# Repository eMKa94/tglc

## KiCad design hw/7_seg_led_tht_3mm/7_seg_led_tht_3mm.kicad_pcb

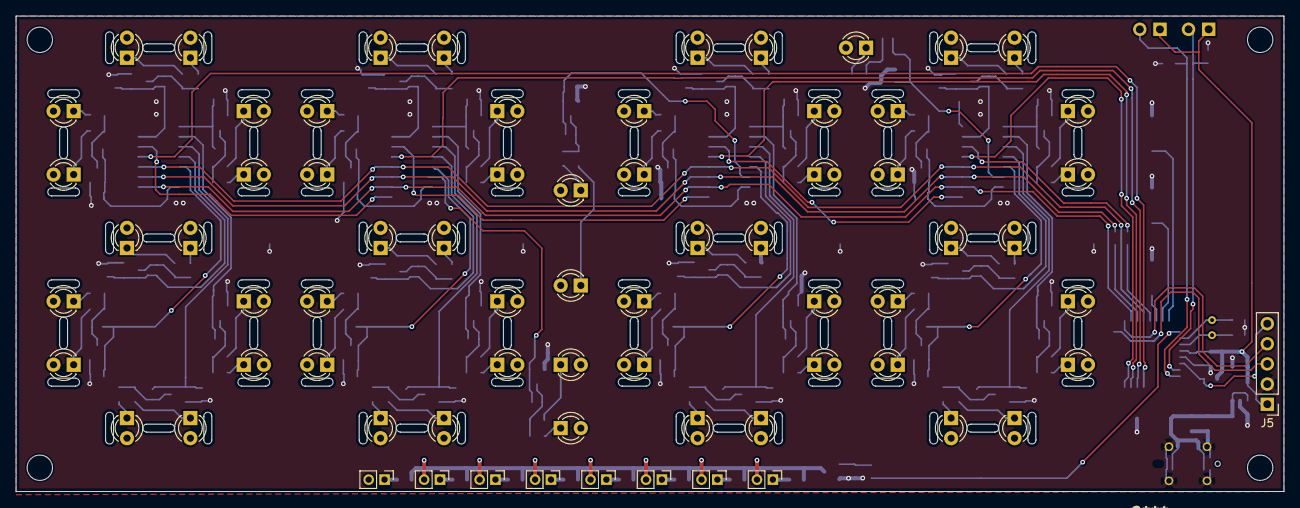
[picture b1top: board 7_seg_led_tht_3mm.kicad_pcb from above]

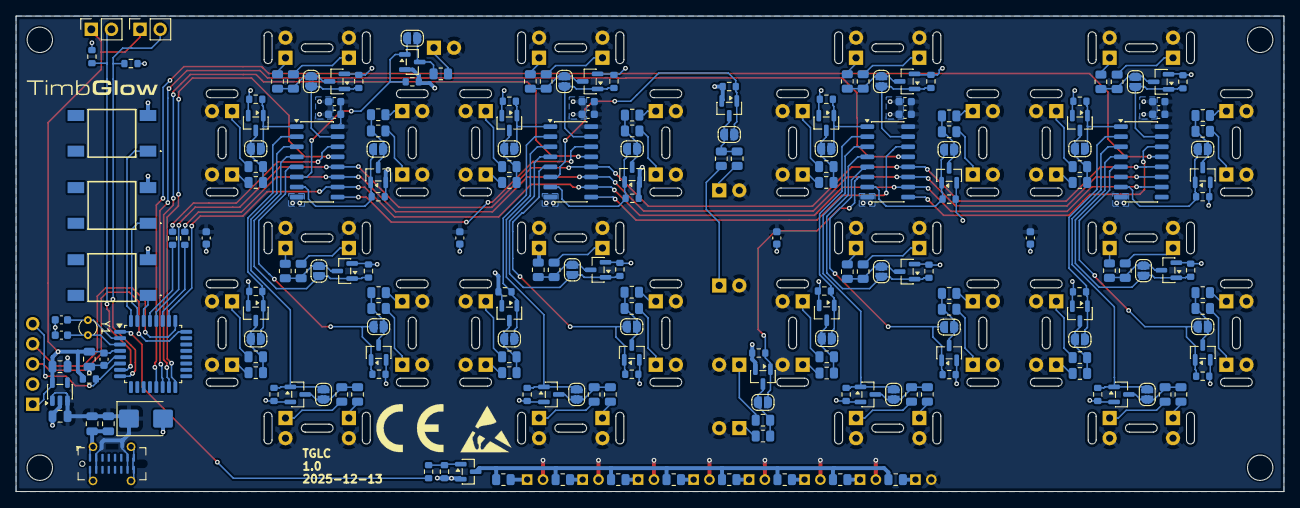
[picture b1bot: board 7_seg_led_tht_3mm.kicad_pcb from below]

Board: 2 copper layers, 160.0 x 60.0 mm, 278 parts (208 on the bottom side), 160 nets.

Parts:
C1, C2: 10u; C_0805_2012Metric
C3, C4, C8: 1u; C_0805_2012Metric
C6, C7: 7p 50V; C_0603_1608Metric
C9, C11, C13, C15, C17: 100n; C_0603_1608Metric
C10, C12, C14, C16, C18, C19, C20, C21: 1u; C_0603_1608Metric
D1: D_Zener; D_SMB
D2, D67, D68, D69, D70, D71, D72, D73: LED; PinHeader_1x02_P2.00mm_Vertical
D3, D4, D5, D6, D7, D8, D9, D10, D11, D12, D13, D14, D15, D16, D17, D19, D20, D21, D22, D23, D24, D25, D26, D27, D28, D29, D30, D31, D32, D33, D34, D35, D36, D37, D38, D39, D40, D41, D42, D43, D44, D45, D46, D47, D48, D49, D50, D51, D52, D53, D54, D55, D56, D57, D58, D59, D60, D61, D62, D63, D64: LED; LED_D3.0mm
H1, H2, H2#2, H2#3: MountingHole; MountingHole_3.2mm_M3
J1: USB_C_Plug_USB2.0; USB_C_Receptacle_G-Switch_GT-USB-7051x
J3, J4: PGM5526; PinSocket_1x02_P2.54mm_Vertical
J5: Conn_01x05; PinHeader_1x05_P2.54mm_Vertical
JP3, JP4, JP5, JP6, JP7, JP8, JP9, JP10, JP11, JP12, JP13, JP14, JP15, JP16, JP17, JP18, JP19, JP20, JP21, JP22, JP23, JP24, JP25, JP26, JP27, JP28, JP29, JP30, JP31, JP32, JP33: Jumper_2_Small_Open; SolderJumper-2_P1.3mm_Open_RoundedPad1.0x1.5mm
Q1, Q2, Q3, Q4, Q5, Q6, Q7, Q8, Q9, Q10, Q11, Q12, Q13, Q14, Q15, Q16, Q17, Q18, Q19, Q20, Q21, Q22, Q23, Q24, Q25, Q26, Q27, Q28, Q29, Q30, Q31, Q33: 2N7002K; SOT-23
R1, R3, R4: 4K7; R_0603_1608Metric
R2, R110, R111: 22; R_0603_1608Metric
R5, R7, R9, R10, R12, R13, R15, R16, R18, R19, R21, R22, R24, R25, R27, R29, R31, R33, R34, R36, R37, R39, R40, R42, R43, R45, R46, R48, R49, R51, R52, R53, R55, R57, R58, R60, R61, R63, R64, R66, R67, R69, R70, R72, R73, R75, R76, R77, R79, R81, R82, R84, R85, R87, R88, R90, R91, R93, R94, R96, R97, R101, R102, R103, R104, R105, R106, R107, R108: R; R_0805_2012Metric
R6, R8, R11, R14, R17, R20, R23, R26, R30, R32, R35, R38, R41, R44, R47, R50, R54, R56, R59, R62, R65, R68, R71, R74, R78, R80, R83, R86, R89, R92, R95, R109: 10K; R_0603_1608Metric
SW1, SW2, SW3: SW_MEC_5E; TS046673BK100SMT
U1: MIC5504-3.3YM5; SOT-23-5
U2: STM32G030K8Tx; LQFP-32_7x7mm_P0.8mm
U3, U4, U5, U6: 74HCT595; SO-16_3.9x9.9mm_P1.27mm
Y1: 32K768; Crystal_C26-LF_D2.1mm_L6.5mm_Vertical

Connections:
+5V: C1.1, C2.1, C3.1, C10.2, C11.2, C12.2, C13.2, C14.2, C15.2, C16.2, C17.2, C18.1, C19.1, C20.1, C21.1, D1.1 (K), D2.2 (A), D3.2 (A), D4.2 (A), D5.2 (A), D6.2 (A), D7.2 (A), D8.2 (A), D9.2 (A), D10.2 (A), D11.2 (A), D12.2 (A), D13.2 (A), D14.2 (A), D15.2 (A), D16.2 (A), D17.2 (A), D19.2 (A), D20.2 (A), D21.2 (A), D22.2 (A), D23.2 (A), D24.2 (A), D25.2 (A), D26.2 (A), D27.2 (A), D28.2 (A), D29.2 (A), D30.2 (A), D31.2 (A), D32.2 (A), D33.2 (A), D34.2 (A), D35.2 (A), D36.2 (A), D37.2 (A), D38.2 (A), D39.2 (A), D40.2 (A), D41.2 (A), D42.2 (A), D43.2 (A), D44.2 (A), D45.2 (A), D46.2 (A), D47.2 (A), D48.2 (A), D49.2 (A), D50.2 (A), D51.2 (A), D52.2 (A), D53.2 (A), D54.2 (A), D55.2 (A), D56.2 (A), D57.2 (A), D58.2 (A), D59.2 (A), D60.2 (A), D61.2 (A), D62.2 (A), D63.2 (A), D64.2 (A), D67.2 (A), D68.2 (A), D69.2 (A), D70.2 (A), D71.2 (A), D72.2 (A), D73.2 (A), J1.A4 (VBUS), J1.A9 (VBUS), J1.B4 (VBUS), J1.B9 (VBUS), U1.1 (VIN), U1.3 (EN), U3.16 (VCC), U4.16 (VCC), U5.16 (VCC), U6.16 (VCC)
/7_SEG_1/A: JP3.2 (B), Q1.3 (D), R5.1, R7.1
/7_SEG_1/B: JP4.2 (B), Q2.3 (D), R9.1, R10.1
/7_SEG_1/C: JP5.2 (B), Q3.3 (D), R12.1, R13.1
/7_SEG_1/D: JP6.2 (B), Q4.3 (D), R15.1, R16.1
/7_SEG_1/E: JP7.2 (B), Q5.3 (D), R18.1, R19.1
/7_SEG_1/F: JP8.2 (B), Q6.3 (D), R21.1, R22.1
/7_SEG_1/G: JP9.2 (B), Q7.3 (D), R24.1, R25.1
/7_SEG_1/H: JP10.2 (B), Q8.3 (D), R27.1
/7_SEG_1/QA: JP3.1 (A), Q1.1 (G), R6.1, U3.15 (QA)
/7_SEG_1/QB: JP4.1 (A), Q2.1 (G), R8.1, U3.1 (QB)
/7_SEG_1/QC: JP5.1 (A), Q3.1 (G), R11.1, U3.2 (QC)
/7_SEG_1/QD: JP6.1 (A), Q4.1 (G), R14.1, U3.3 (QD)
/7_SEG_1/QE: JP7.1 (A), Q5.1 (G), R17.1, U3.5 (QF)
/7_SEG_1/QF: JP8.1 (A), Q6.1 (G), R20.1, U3.7 (QH)
/7_SEG_1/QG: JP9.1 (A), Q7.1 (G), R23.1, U3.4 (QE)
/7_SEG_1/QH: JP10.1 (A), Q8.1 (G), R26.1, U3.6 (QG)
/7_SEG_2/A: JP11.2 (B), Q9.3 (D), R29.1, R31.1
/7_SEG_2/B: JP12.2 (B), Q10.3 (D), R33.1, R34.1
/7_SEG_2/C: JP13.2 (B), Q11.3 (D), R36.1, R37.1
/7_SEG_2/D: JP14.2 (B), Q12.3 (D), R39.1, R40.1
/7_SEG_2/E: JP15.2 (B), Q13.3 (D), R42.1, R43.1
/7_SEG_2/F: JP16.2 (B), Q14.3 (D), R45.1, R46.1
/7_SEG_2/G: JP17.2 (B), Q15.3 (D), R48.1, R49.1
/7_SEG_2/H: JP18.2 (B), Q16.3 (D), R51.1, R52.1
/7_SEG_2/QA: JP11.1 (A), Q9.1 (G), R30.1, U4.15 (QA)
/7_SEG_2/QB: JP12.1 (A), Q10.1 (G), R32.1, U4.1 (QB)
/7_SEG_2/QC: JP13.1 (A), Q11.1 (G), R35.1, U4.2 (QC)
/7_SEG_2/QD: JP14.1 (A), Q12.1 (G), R38.1, U4.3 (QD)
/7_SEG_2/QE: JP15.1 (A), Q13.1 (G), R41.1, U4.5 (QF)
/7_SEG_2/QF: JP16.1 (A), Q14.1 (G), R44.1, U4.7 (QH)
/7_SEG_2/QG: JP17.1 (A), Q15.1 (G), R47.1, U4.4 (QE)
/7_SEG_2/QH: JP18.1 (A), Q16.1 (G), R50.1, U4.6 (QG)
/7_SEG_3/A: JP19.2 (B), Q17.3 (D), R53.1, R55.1
/7_SEG_3/B: JP20.2 (B), Q18.3 (D), R57.1, R58.1
/7_SEG_3/C: JP21.2 (B), Q19.3 (D), R60.1, R61.1
/7_SEG_3/D: JP22.2 (B), Q20.3 (D), R63.1, R64.1
/7_SEG_3/E: JP23.2 (B), Q21.3 (D), R66.1, R67.1
/7_SEG_3/F: JP24.2 (B), Q22.3 (D), R69.1, R70.1
/7_SEG_3/G: JP25.2 (B), Q23.3 (D), R72.1, R73.1
/7_SEG_3/H: JP26.2 (B), Q24.3 (D), R75.1, R76.1
/7_SEG_3/QA: JP19.1 (A), Q17.1 (G), R54.1, U5.15 (QA)
/7_SEG_3/QB: JP20.1 (A), Q18.1 (G), R56.1, U5.1 (QB)
/7_SEG_3/QC: JP21.1 (A), Q19.1 (G), R59.1, U5.2 (QC)
/7_SEG_3/QD: JP22.1 (A), Q20.1 (G), R62.1, U5.3 (QD)
/7_SEG_3/QE: JP23.1 (A), Q21.1 (G), R65.1, U5.5 (QF)
/7_SEG_3/QF: JP24.1 (A), Q22.1 (G), R68.1, U5.7 (QH)
/7_SEG_3/QG: JP25.1 (A), Q23.1 (G), R71.1, U5.4 (QE)
/7_SEG_3/QH: JP26.1 (A), Q24.1 (G), R74.1, U5.6 (QG)
/7_SEG_4/A: JP27.2 (B), Q25.3 (D), R77.1, R79.1
/7_SEG_4/B: JP28.2 (B), Q26.3 (D), R81.1, R82.1
/7_SEG_4/C: JP29.2 (B), Q27.3 (D), R84.1, R85.1
/7_SEG_4/D: JP30.2 (B), Q28.3 (D), R87.1, R88.1
/7_SEG_4/E: JP31.2 (B), Q29.3 (D), R90.1, R91.1
/7_SEG_4/F: JP32.2 (B), Q30.3 (D), R93.1, R94.1
/7_SEG_4/G: JP33.2 (B), Q31.3 (D), R96.1, R97.1
/7_SEG_4/QA: JP27.1 (A), Q25.1 (G), R78.1, U6.15 (QA)
/7_SEG_4/QB: JP28.1 (A), Q26.1 (G), R80.1, U6.1 (QB)
/7_SEG_4/QC: JP29.1 (A), Q27.1 (G), R83.1, U6.2 (QC)
/7_SEG_4/QD: JP30.1 (A), Q28.1 (G), R86.1, U6.3 (QD)
/7_SEG_4/QE: JP31.1 (A), Q29.1 (G), R89.1, U6.5 (QF)
/7_SEG_4/QF: JP32.1 (A), Q30.1 (G), R92.1, U6.7 (QH)
/7_SEG_4/QG: JP33.1 (A), Q31.1 (G), R95.1, U6.4 (QE)
/ T_{NRST}: J5.5, R3.2, U2.6 (NRST)
/DISP_RESET: U2.26 (PA15), U3.10 (~SRCLR), U4.10 (~SRCLR), U5.10 (~SRCLR), U6.10 (~SRCLR)
/FD_analog: J4.2, R1.1, U2.7 (PA0)
/LOGO_PWM: R110.1, U2.1 (TIM17_CH1)
/PUSH_OUT: U2.28 (PB4), U3.12 (RCLK), U4.12 (RCLK), U5.12 (RCLK), U6.12 (RCLK)
/PWM_DIG_1: U2.16 (TIM3_CH4), U3.13 (~OE)
/PWM_DIG_2: U2.15 (TIM3_CH3), U4.13 (~OE)
/PWM_DIG_3: U2.14 (TIM3_CH2), U5.13 (~OE)
/PWM_DIG_4: U2.13 (TIM3_CH1), U6.13 (~OE)
/SPI_MOSI: R2.2, U3.14 (SER)
/SPI_SCK: R111.2, U3.11 (SRCLK), U4.11 (SRCLK), U5.11 (SRCLK), U6.11 (SRCLK)
/SR1_OUT: U3.9 (QH'), U4.14 (SER)
/SR2_OUT: U4.9 (QH'), U5.14 (SER)
/SR3_OUT: U5.9 (QH'), U6.14 (SER)
/SW_1: SW1.1, U2.32 (PB8)
/SW_2: SW2.1, U2.31 (PB7)
/SW_3: SW3.1, U2.30 (PB6)
/SW_CLK: J5.4, U2.25 (PA14)
/SW_DIO: J5.3, U2.24 (PA13)
/TEMP_analog: J3.2, R4.1, U2.8 (PA1)
GND: C1.2, C2.2, C3.2, C4.2, C6.2, C7.2, C8.2, C9.2, C10.1, C11.1, C12.1, C13.1, C14.1, C15.1, C16.1, C17.1, C18.2, C19.2, C20.2, C21.2, D1.2 (A), J1.A1 (GND), J1.A12 (GND), J1.B1 (GND), J1.B12 (GND), J1.S1 (SHIELD), J5.2, Q1.2 (S), Q2.2 (S), Q3.2 (S), Q4.2 (S), Q5.2 (S), Q6.2 (S), Q7.2 (S), Q8.2 (S), Q9.2 (S), Q10.2 (S), Q11.2 (S), Q12.2 (S), Q13.2 (S), Q14.2 (S), Q15.2 (S), Q16.2 (S), Q17.2 (S), Q18.2 (S), Q19.2 (S), Q20.2 (S), Q21.2 (S), Q22.2 (S), Q23.2 (S), Q24.2 (S), Q25.2 (S), Q26.2 (S), Q27.2 (S), Q28.2 (S), Q29.2 (S), Q30.2 (S), Q31.2 (S), Q33.2 (S), R1.2, R4.2, R6.2, R8.2, R11.2, R14.2, R17.2, R20.2, R23.2, R26.2, R30.2, R32.2, R35.2, R38.2, R41.2, R44.2, R47.2, R50.2, R54.2, R56.2, R59.2, R62.2, R65.2, R68.2, R71.2, R74.2, R78.2, R80.2, R83.2, R86.2, R89.2, R92.2, R95.2, R109.2, SW1.3 (K), SW2.3 (K), SW3.3 (K), U1.2 (GND), U2.5 (VSS), U3.8 (GND), U4.8 (GND), U5.8 (GND), U6.8 (GND)
unnamed: D2.1 (K), R102.1
unnamed: D3.1 (K), R5.2
unnamed: D4.1 (K), R7.2
unnamed: D5.1 (K), R9.2
unnamed: D6.1 (K), R10.2
unnamed: D7.1 (K), R12.2
unnamed: D8.1 (K), R13.2
unnamed: D9.1 (K), R15.2
unnamed: D10.1 (K), R16.2
unnamed: D11.1 (K), R18.2
unnamed: D12.1 (K), R19.2
unnamed: D13.1 (K), R21.2
unnamed: D14.1 (K), R22.2
unnamed: D15.1 (K), R24.2
unnamed: D16.1 (K), R25.2
unnamed: D17.1 (K), R27.2
unnamed: D19.1 (K), R29.2
unnamed: D20.1 (K), R31.2
unnamed: D21.1 (K), R33.2
unnamed: D22.1 (K), R34.2
unnamed: D23.1 (K), R36.2
unnamed: D24.1 (K), R37.2
unnamed: D25.1 (K), R39.2
unnamed: D26.1 (K), R40.2
unnamed: D27.1 (K), R42.2
unnamed: D28.1 (K), R43.2
unnamed: D29.1 (K), R45.2
unnamed: D30.1 (K), R46.2
unnamed: D31.1 (K), R48.2
unnamed: D32.1 (K), R49.2
unnamed: D33.1 (K), R51.2
unnamed: D34.1 (K), R52.2
unnamed: D35.1 (K), R53.2
unnamed: D36.1 (K), R55.2
unnamed: D37.1 (K), R57.2
unnamed: D38.1 (K), R58.2
unnamed: D39.1 (K), R60.2
unnamed: D40.1 (K), R61.2
unnamed: D41.1 (K), R63.2
unnamed: D42.1 (K), R64.2
unnamed: D43.1 (K), R66.2
unnamed: D44.1 (K), R67.2
unnamed: D45.1 (K), R69.2
unnamed: D46.1 (K), R70.2
unnamed: D47.1 (K), R72.2
unnamed: D48.1 (K), R73.2
unnamed: D49.1 (K), R75.2
unnamed: D50.1 (K), R76.2
unnamed: D51.1 (K), R77.2
unnamed: D52.1 (K), R79.2
unnamed: D53.1 (K), R81.2
unnamed: D54.1 (K), R82.2
unnamed: D55.1 (K), R84.2
unnamed: D56.1 (K), R85.2
unnamed: D57.1 (K), R87.2
unnamed: D58.1 (K), R88.2
unnamed: D59.1 (K), R90.2
unnamed: D60.1 (K), R91.2
unnamed: D61.1 (K), R93.2
unnamed: D62.1 (K), R94.2
unnamed: D63.1 (K), R96.2
unnamed: D64.1 (K), R97.2
unnamed: D67.1 (K), R101.1
unnamed: D68.1 (K), R103.1
unnamed: D69.1 (K), R104.1
unnamed: D70.1 (K), R105.1
unnamed: D71.1 (K), R106.1
unnamed: D72.1 (K), R107.1
unnamed: D73.1 (K), R108.1
unnamed: Q33.3 (D), R101.2, R102.2, R103.2, R104.2, R105.2, R106.2, R107.2, R108.2
unnamed: Q33.1 (G), R109.1, R110.2
unnamed: R111.1, U2.27 (SPI1_SCK)
unnamed: R2.1, U2.29 (SPI1_MOSI)
unnamed: C6.1, U2.2 (PC14), Y1.1
unnamed: C7.1, U2.3 (PC15), Y1.2
VDD: C4.1, C8.1, C9.1, J3.1, J4.1, J5.1, R3.1, U1.5 (VOUT), U2.4 (VDD)

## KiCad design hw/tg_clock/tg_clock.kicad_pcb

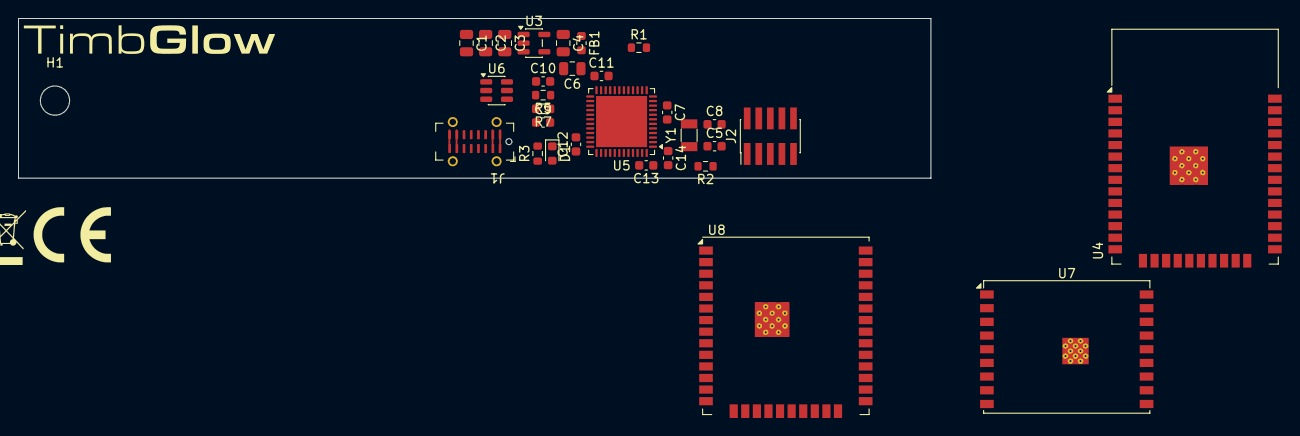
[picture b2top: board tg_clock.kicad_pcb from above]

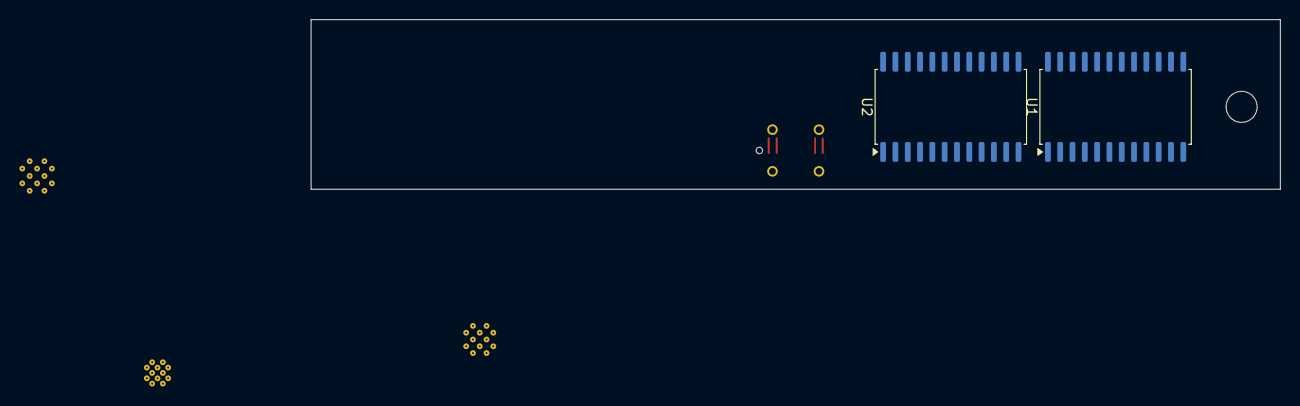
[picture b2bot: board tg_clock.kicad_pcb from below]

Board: 4 copper layers, 100.0 x 17.5 mm, 34 parts (2 on the bottom side), 19 nets.

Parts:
C1, C2: 10u; C_0805_2012Metric
C3, C4, C6: 1u; C_0805_2012Metric
C5, C8: 7p 50V; C_0603_1608Metric
C7, C11, C12, C13, C14: 100n; C_0603_1608Metric
C9, C10: 47p; C_0603_1608Metric
D1: GREEN; LED_0603_1608Metric
FB1: Xm; L_0603_1608Metric
H1, H2: MountingHole; MountingHole_3.2mm_M3
J1: USB_C_Plug_USB2.0; USB_C_Receptacle_G-Switch_GT-USB-7051x
J2: Conn_02x05_Odd_Even; PinHeader_2x05_P1.27mm_Vertical_SMD
R1, R2: 4K7; R_0603_1608Metric
R3: 390; R_0603_1608Metric
R5, R7: 22; R_0603_1608Metric
U1, U2: STP16CPC26M; SOIC-24W_7.5x15.4mm_P1.27mm
U3: MIC5504-3.3YM5; SOT-23-5
U4: ESP32-WROOM-32
U5: STM32L053C8Ux; QFN-48-1EP_7x7mm_P0.5mm_EP5.6x5.6mm
U6: USBLC6-2SC6; SOT-23-6
U7: ESP32-C3-WROOM-02U
U8: ESP32-WROOM-32U
Y1: 32K768; Crystal_SMD_3215-2Pin_3.2x1.5mm

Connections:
+5V: C1.1, C2.1, C3.1, J1.A4 (VBUS), J1.A9 (VBUS), J1.B4 (VBUS), J1.B9 (VBUS), U3.1 (VIN), U3.3 (EN), U6.5 (VBUS)
/ T_{NRST}: J2.10, R2.2, U5.7 (NRST)
/SW_CLK: J2.4, U5.37 (PA14)
/SW_DIO: J2.2, U5.34 (PA13)
/USB_D+: R5.1, U5.31 (PA10)
/USB_D-: R7.1, U5.32 (PA11)
GND: C1.2, C2.2, C3.2, C4.2, C5.2, C6.2, C7.2, C8.2, C9.2, C10.2, C11.2, C12.2, C13.2, C14.2, J1.A1 (GND), J1.A12 (GND), J1.B1 (GND), J1.B12 (GND), J1.S1 (SHIELD), J2.3, J2.5, R1.2, R3.1, U3.2 (GND), U5.8 (VSSA), U5.23 (VSS), U5.35 (VSS), U5.44 (BOOT0), U5.47 (VSS), U5.49 (VSS), U6.2 (GND)
unnamed: C9.1, R7.2, U6.4 (I/O2)
unnamed: C10.1, R5.2, U6.6 (I/O1)
unnamed: D1.1 (K), R3.2
unnamed: J1.A6 (D+), J1.B6 (D+), U6.1 (I/O1)
unnamed: J1.A7 (D-), J1.B7 (D-), U6.3 (I/O2)
unnamed: U4.1 (GND), U4.15 (GND), U4.38 (GND), U4.39 (GND)
unnamed: C5.1, U5.3 (PC14), Y1.2
unnamed: C8.1, U5.4 (PC15), Y1.1
unnamed: C6.1, C7.1, C11.1, C12.1, C13.1, C14.1, FB1.2, U5.1 (VLCD), U5.9 (VDDA), U5.24 (VDD), U5.36 (VDD_USB), U5.48 (VDD)
unnamed: U7.9 (GND), U7.19 (GND)
unnamed: U8.1 (GND), U8.15 (GND), U8.38 (GND), U8.39 (GND)
VDD: C4.1, FB1.1, J2.1, R2.1, U3.5 (VOUT)

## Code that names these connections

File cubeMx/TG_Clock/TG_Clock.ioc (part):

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Mcu.Name=STM32G030K(6-8)Tx
Mcu.Package=LQFP32
Mcu.UserName=STM32G030K8Tx
PA0.Mode=IN0
PA0.Signal=ADC1_IN0
PA1.Mode=IN1
PA1.Signal=ADC1_IN1
PA13.Mode=Serial_Wire
PA13.Signal=SYS_SWDIO
PA14-BOOT0.Mode=Serial_Wire
PA14-BOOT0.Signal=SYS_SWCLK
PA15.GPIOParameters=GPIO_Label
PA15.GPIO_Label=DISP_RESET
PA15.Signal=GPIO_Output
PA6.GPIOParameters=GPIO_Label
PA6.GPIO_Label=PWM_DIG_4
PA6.Signal=GPIO_Output
PA7.GPIOParameters=GPIO_Label
PA7.GPIO_Label=PWM_DIG_3
PA7.Signal=GPIO_Output
PB0.GPIOParameters=GPIO_Label
PB0.GPIO_Label=PWM_DIG_2
PB0.Signal=GPIO_Output
PB1.GPIOParameters=GPIO_Label
PB1.GPIO_Label=PWM_DIG_1
PB1.Signal=GPIO_Output
PB3.GPIOParameters=GPIO_Label
PB3.GPIO_Label=DISPLAY_SCK
PB3.Mode=TX_Only_Simplex_Unidirect_Master
PB3.Signal=SPI1_SCK
PB4.GPIOParameters=GPIO_Label
PB4.GPIO_Label=PUSH_OUT
PB4.Signal=GPIO_Output
PB5.GPIOParameters=GPIO_Label
PB5.GPIO_Label=DISPLAY_MOSI
PB5.Mode=TX_Only_Simplex_Unidirect_Master
PB5.Signal=SPI1_MOSI
PB6.Signal=GPIO_Input
PB7.Signal=GPIO_Input
PB8.Signal=GPIO_Input
PC14-OSC32_IN\ (PC14).Mode=LSE-External-Oscillator
PC14-OSC32_IN\ (PC14).Signal=RCC_OSC32_IN
PC15-OSC32_OUT\ (PC15).Mode=LSE-External-Oscillator
PC15-OSC32_OUT\ (PC15).Signal=RCC_OSC32_OUT
RCC.HSE_VALUE=8000000
RCC.SYSCLKFreq_VALUE=64000000
RCC.SYSCLKSource=RCC_SYSCLKSOURCE_PLLCLK
board=custom

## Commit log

2026-01-09 Firmware draft, working animations
2026-01-09 better animations and hw files
2026-01-18 LSE and RTC from MX
2026-01-18 RTC Time display
